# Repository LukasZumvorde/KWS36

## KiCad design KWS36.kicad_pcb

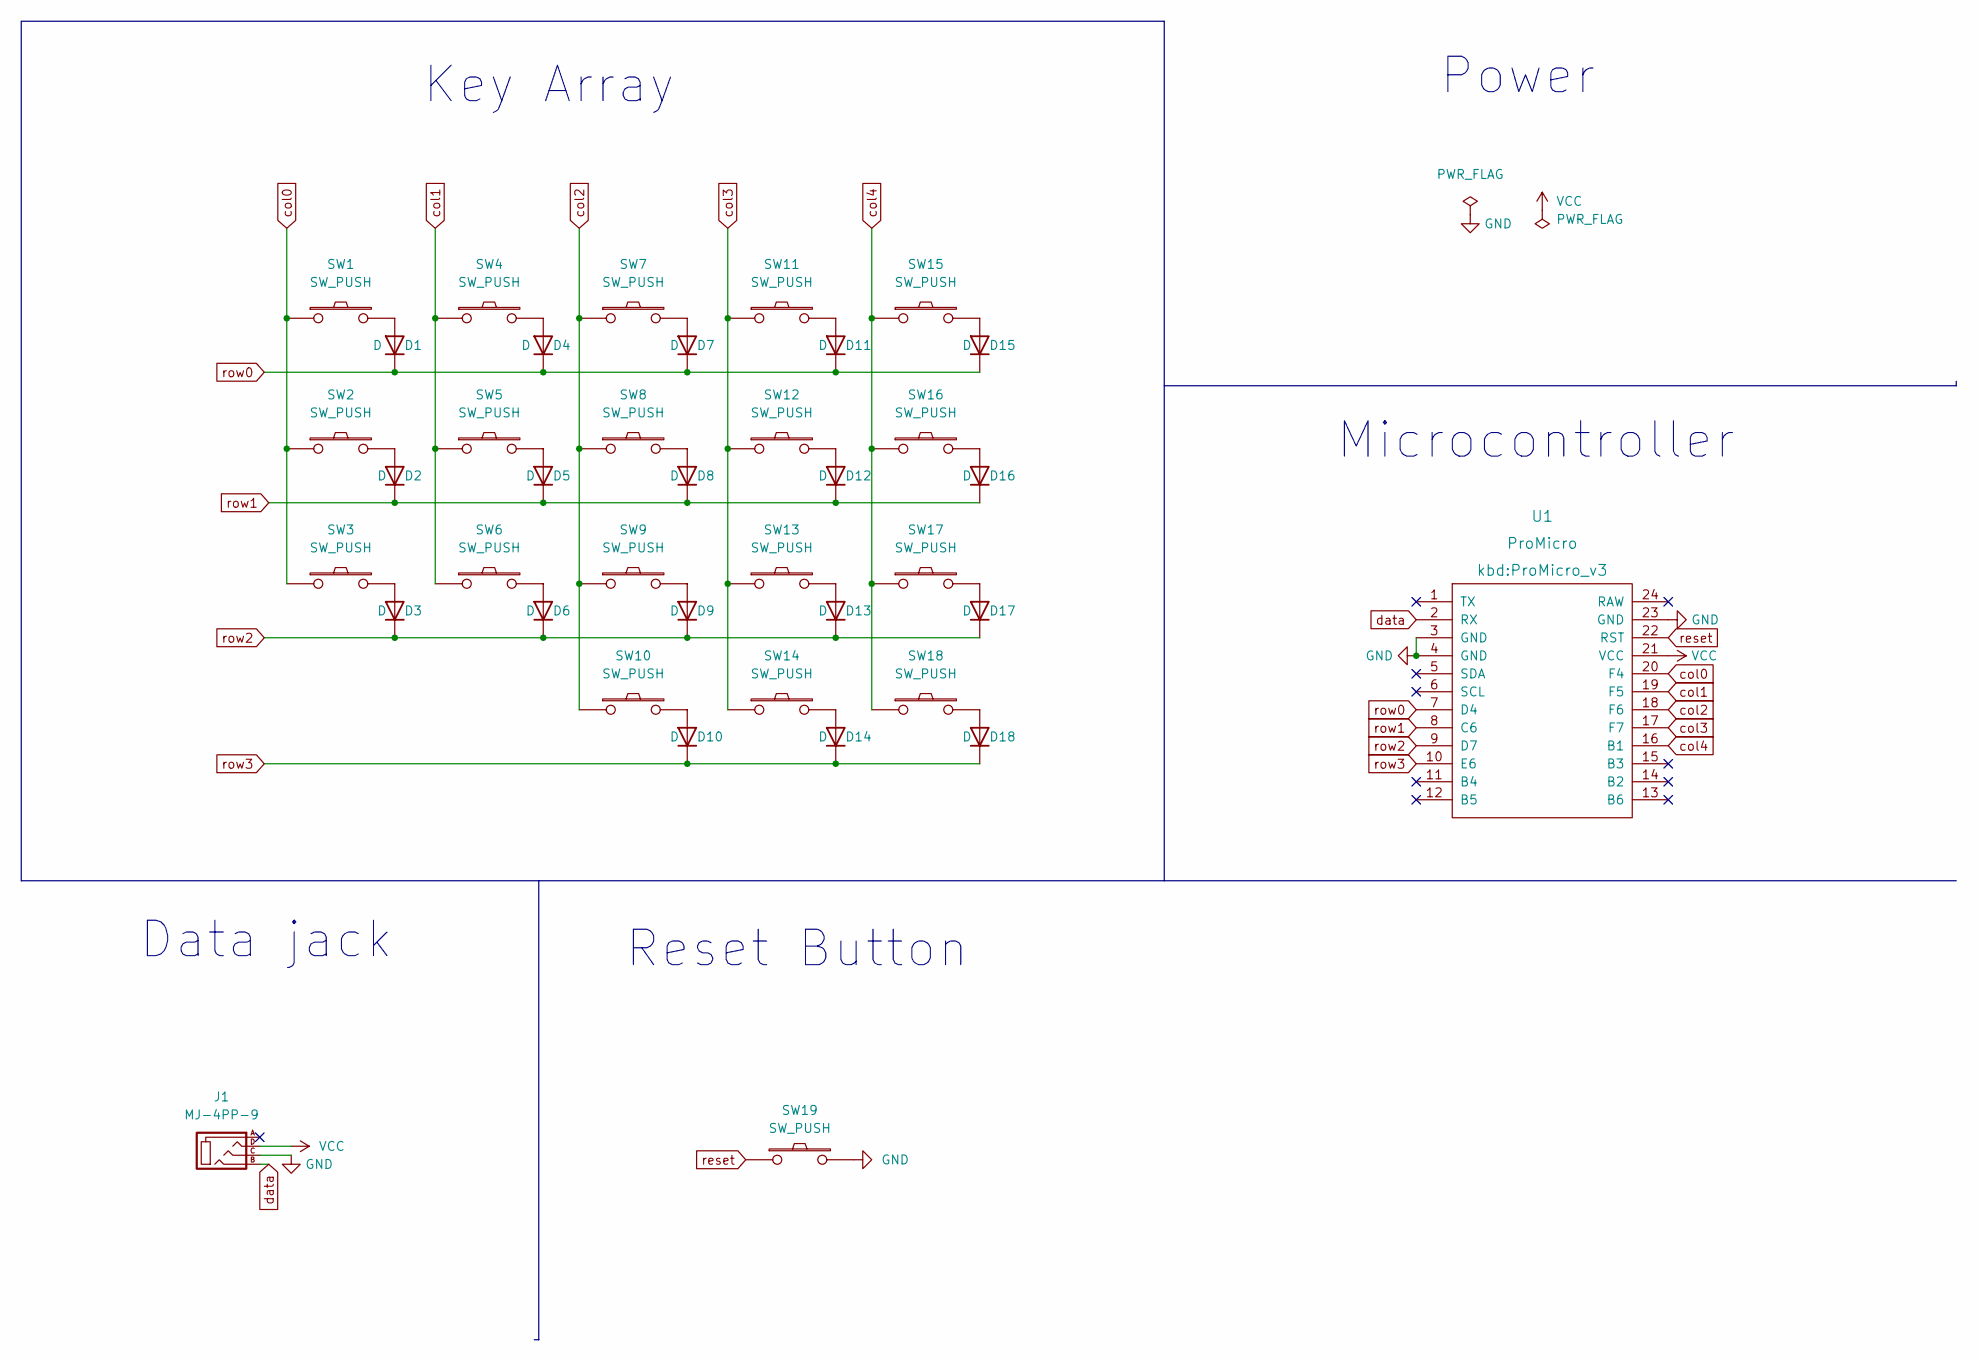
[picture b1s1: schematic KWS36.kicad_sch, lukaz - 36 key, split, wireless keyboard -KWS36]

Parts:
D1, D2, D3, D4, D5, D6, D7, D8, D9, D10, D11, D12, D13, D14, D15, D16, D17, D18: D; D3_TH
J1: MJ-4PP-9
SW1, SW2, SW3, SW4, SW5, SW6, SW7, SW8, SW9, SW10, SW11, SW12, SW13, SW14, SW15, SW16, SW17, SW18: SW_PUSH; SW_Kailh_Choc_V1V2_1.00u_flippable
SW19: SW_PUSH; ResetSW_1side
U1: ProMicro; ProMicro_v3

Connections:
GND: J1.C, SW19.2, U1.3 (GND), U1.4 (GND), U1.23 (GND)
unnamed: D1.2 (A), SW1.2
unnamed: D2.2 (A), SW2.2
unnamed: D3.2 (A), SW3.2
unnamed: D4.2 (A), SW4.2
unnamed: D5.2 (A), SW5.2
unnamed: D6.2 (A), SW6.2
unnamed: D7.2 (A), SW7.2
unnamed: D8.2 (A), SW8.2
unnamed: D9.2 (A), SW9.2
unnamed: D10.2 (A), SW10.2
unnamed: D11.2 (A), SW11.2
unnamed: D12.2 (A), SW12.2
unnamed: D13.2 (A), SW13.2
unnamed: D14.2 (A), SW14.2
unnamed: D15.2 (A), SW15.2
unnamed: D16.2 (A), SW16.2
unnamed: D17.2 (A), SW17.2
unnamed: D18.2 (A), SW18.2
VCC: J1.D, U1.21 (VCC)
col0: SW1.1, SW2.1, SW3.1, U1.20 (F4)
col1: SW4.1, SW5.1, SW6.1, U1.19 (F5)
col2: SW7.1, SW8.1, SW9.1, SW10.1, U1.18 (F6)
col3: SW11.1, SW12.1, SW13.1, SW14.1, U1.17 (F7)
col4: SW15.1, SW16.1, SW17.1, SW18.1, U1.16 (B1)
data: J1.B, U1.2 (RX)
reset: SW19.1, U1.22 (RST)
row0: D1.1 (K), D4.1 (K), D7.1 (K), D11.1 (K), D15.1 (K), U1.7 (D4)
row1: D2.1 (K), D5.1 (K), D8.1 (K), D12.1 (K), D16.1 (K), U1.8 (C6)
row2: D3.1 (K), D6.1 (K), D9.1 (K), D13.1 (K), D17.1 (K), U1.9 (D7)
row3: D10.1 (K), D14.1 (K), D18.1 (K), U1.10 (E6)

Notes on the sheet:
Reset Button
Data jack
Power
Microcontroller
Key Array

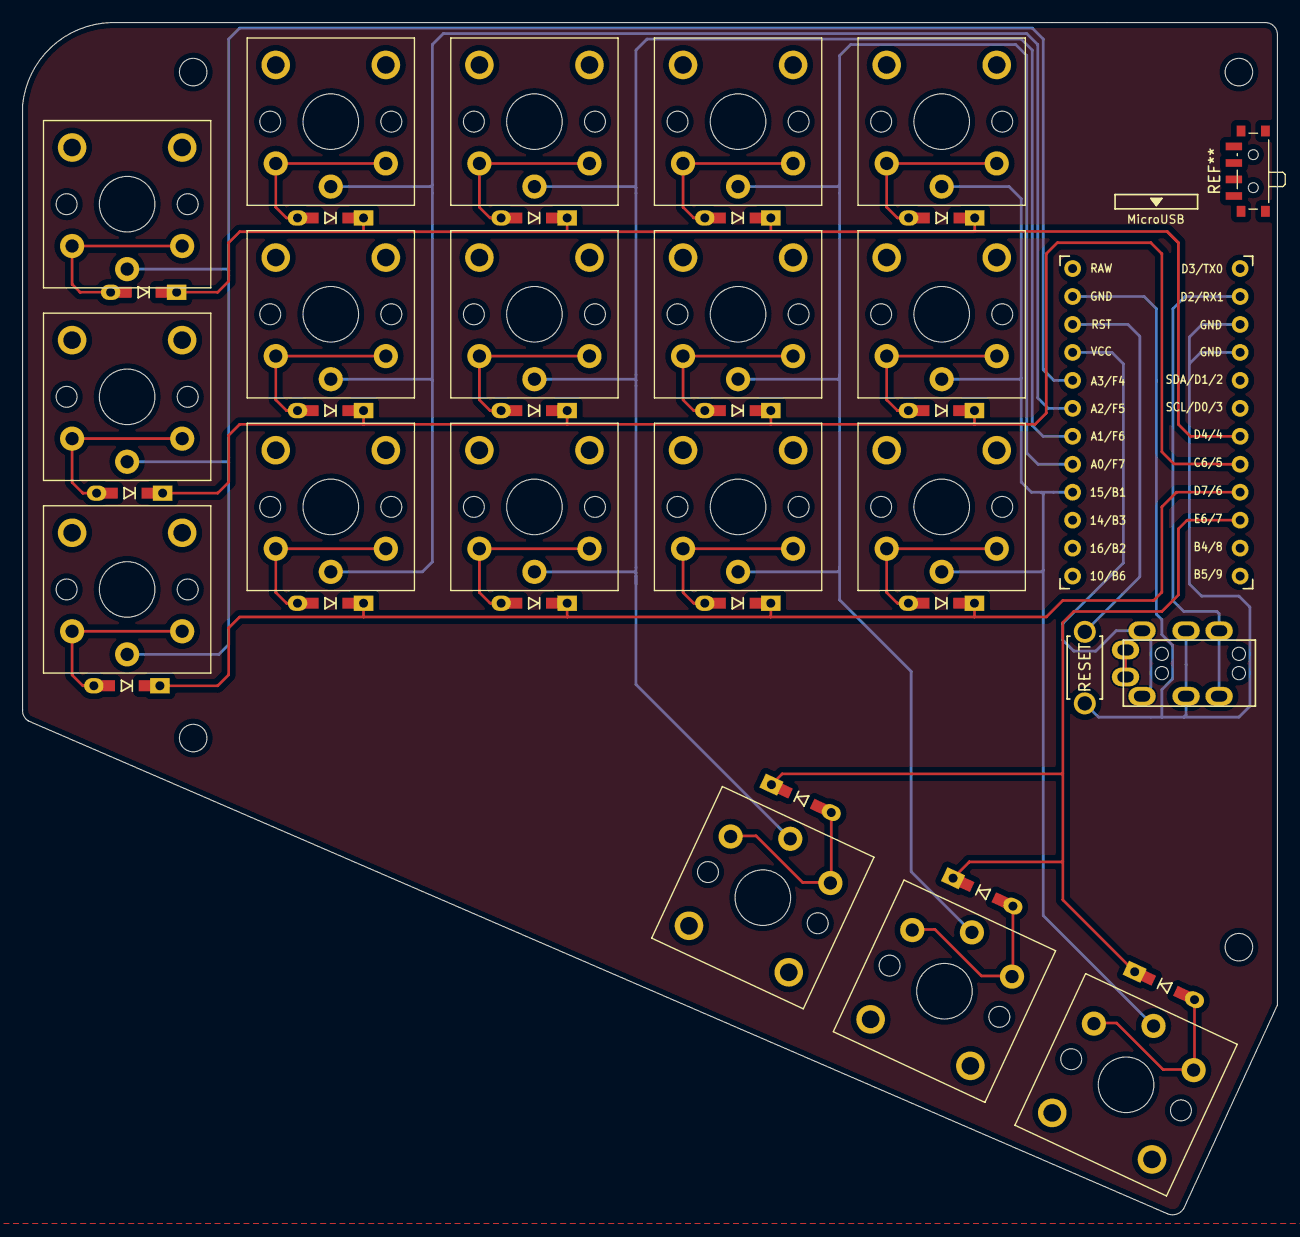
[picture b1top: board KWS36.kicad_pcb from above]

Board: 2 copper layers, 114.0 x 108.3 mm, 39 parts (0 on the bottom side), 31 nets.

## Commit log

2022-08-08 inital commit
